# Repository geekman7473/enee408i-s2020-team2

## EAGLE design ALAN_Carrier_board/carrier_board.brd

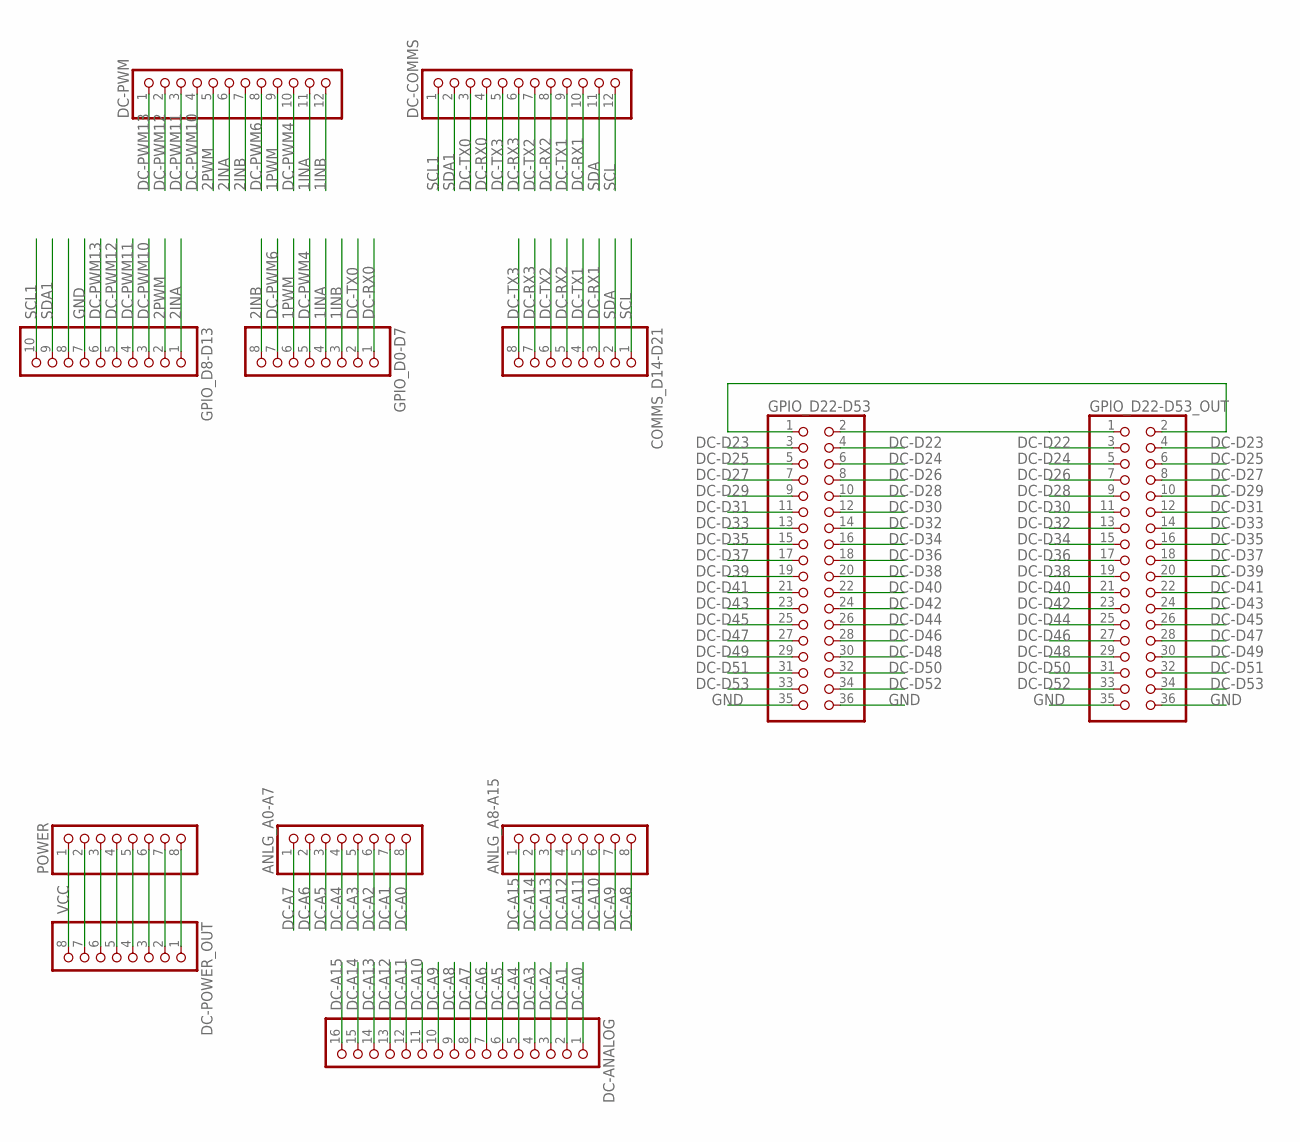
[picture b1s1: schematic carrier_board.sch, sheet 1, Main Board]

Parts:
ANLG_A0-A7, ANLG_A8-A15: PINHD-1X8; 1X08
COMMS_D14-D21: PINHD-1X8; 1X08
DC-ANALOG: PINHD-1X16; 1X16
DC-COMMS: PINHD-1X12; 1X12
DC-POWER_OUT: PINHD-1X8; 1X08
DC-PWM: PINHD-1X12; 1X12
GPIO_D0-D7: PINHD-1X8; 1X08
GPIO_D8-D13: PINHD-1X10; 1X10
GPIO_D22-D53, GPIO_D22-D53_OUT: PINHD-2X18; 2X18
POWER: PINHD-1X8; 1X08

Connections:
1INA: DC-PWM.11, GPIO_D0-D7.4; also elsewhere on the board
1INB: DC-PWM.12, GPIO_D0-D7.3; also elsewhere on the board
1PWM: DC-PWM.9, GPIO_D0-D7.6; also elsewhere on the board
2INA: DC-PWM.6, GPIO_D8-D13.1; also elsewhere on the board
2INB: DC-PWM.7, GPIO_D0-D7.8; also elsewhere on the board
2PWM: DC-PWM.5, GPIO_D8-D13.2; also elsewhere on the board
DC-A0: ANLG_A0-A7.8, DC-ANALOG.1
DC-A1: ANLG_A0-A7.7, DC-ANALOG.2
DC-A2: ANLG_A0-A7.6, DC-ANALOG.3
DC-A3: ANLG_A0-A7.5, DC-ANALOG.4
DC-A4: ANLG_A0-A7.4, DC-ANALOG.5
DC-A5: ANLG_A0-A7.3, DC-ANALOG.6
DC-A6: ANLG_A0-A7.2, DC-ANALOG.7
DC-A7: ANLG_A0-A7.1, DC-ANALOG.8
DC-A8: ANLG_A8-A15.8, DC-ANALOG.9
DC-A9: ANLG_A8-A15.7, DC-ANALOG.10
DC-A10: ANLG_A8-A15.6, DC-ANALOG.11
DC-A11: ANLG_A8-A15.5, DC-ANALOG.12
DC-A12: ANLG_A8-A15.4, DC-ANALOG.13
DC-A13: ANLG_A8-A15.3, DC-ANALOG.14
DC-A14: ANLG_A8-A15.2, DC-ANALOG.15
DC-A15: ANLG_A8-A15.1, DC-ANALOG.16
DC-D22: GPIO_D22-D53.4, GPIO_D22-D53_OUT.3
DC-D23: GPIO_D22-D53.3, GPIO_D22-D53_OUT.4
DC-D24: GPIO_D22-D53.6, GPIO_D22-D53_OUT.5
DC-D25: GPIO_D22-D53.5, GPIO_D22-D53_OUT.6
DC-D26: GPIO_D22-D53.8, GPIO_D22-D53_OUT.7
DC-D27: GPIO_D22-D53.7, GPIO_D22-D53_OUT.8
DC-D28: GPIO_D22-D53.10, GPIO_D22-D53_OUT.9
DC-D29: GPIO_D22-D53.9, GPIO_D22-D53_OUT.10
DC-D30: GPIO_D22-D53.12, GPIO_D22-D53_OUT.11
DC-D31: GPIO_D22-D53.11, GPIO_D22-D53_OUT.12
DC-D32: GPIO_D22-D53.14, GPIO_D22-D53_OUT.13
DC-D33: GPIO_D22-D53.13, GPIO_D22-D53_OUT.14
DC-D34: GPIO_D22-D53.16, GPIO_D22-D53_OUT.15
DC-D35: GPIO_D22-D53.15, GPIO_D22-D53_OUT.16
DC-D36: GPIO_D22-D53.18, GPIO_D22-D53_OUT.17
DC-D37: GPIO_D22-D53.17, GPIO_D22-D53_OUT.18
DC-D38: GPIO_D22-D53.20, GPIO_D22-D53_OUT.19
DC-D39: GPIO_D22-D53.19, GPIO_D22-D53_OUT.20
DC-D40: GPIO_D22-D53.22, GPIO_D22-D53_OUT.21
DC-D41: GPIO_D22-D53.21, GPIO_D22-D53_OUT.22
DC-D42: GPIO_D22-D53.24, GPIO_D22-D53_OUT.23
DC-D43: GPIO_D22-D53.23, GPIO_D22-D53_OUT.24
DC-D44: GPIO_D22-D53.26, GPIO_D22-D53_OUT.25
DC-D45: GPIO_D22-D53.25, GPIO_D22-D53_OUT.26
DC-D46: GPIO_D22-D53.28, GPIO_D22-D53_OUT.27
DC-D47: GPIO_D22-D53.27, GPIO_D22-D53_OUT.28
DC-D48: GPIO_D22-D53.30, GPIO_D22-D53_OUT.29
DC-D49: GPIO_D22-D53.29, GPIO_D22-D53_OUT.30
DC-D50: GPIO_D22-D53.32, GPIO_D22-D53_OUT.31
DC-D51: GPIO_D22-D53.31, GPIO_D22-D53_OUT.32
DC-D52: GPIO_D22-D53.34, GPIO_D22-D53_OUT.33
DC-D53: GPIO_D22-D53.33, GPIO_D22-D53_OUT.34
DC-PWM4: DC-PWM.10, GPIO_D0-D7.5
DC-PWM6: DC-PWM.8, GPIO_D0-D7.7
DC-PWM10: DC-PWM.4, GPIO_D8-D13.3
DC-PWM11: DC-PWM.3, GPIO_D8-D13.4
DC-PWM12: DC-PWM.2, GPIO_D8-D13.5
DC-PWM13: DC-PWM.1, GPIO_D8-D13.6
DC-RX0: DC-COMMS.4, GPIO_D0-D7.1
DC-RX1: COMMS_D14-D21.3, DC-COMMS.10
DC-RX2: COMMS_D14-D21.5, DC-COMMS.8
DC-RX3: COMMS_D14-D21.7, DC-COMMS.6
DC-TX0: DC-COMMS.3, GPIO_D0-D7.2
DC-TX1: COMMS_D14-D21.4, DC-COMMS.9
DC-TX2: COMMS_D14-D21.6, DC-COMMS.7
DC-TX3: COMMS_D14-D21.8, DC-COMMS.5
GND: GPIO_D8-D13.7, GPIO_D22-D53.35, GPIO_D22-D53.36, GPIO_D22-D53_OUT.35, GPIO_D22-D53_OUT.36; also elsewhere on the board
unnamed: GPIO_D22-D53.1, GPIO_D22-D53_OUT.2
unnamed: GPIO_D22-D53.2, GPIO_D22-D53_OUT.1
unnamed: DC-POWER_OUT.1, POWER.8
unnamed: DC-POWER_OUT.2, POWER.7
unnamed: DC-POWER_OUT.3, POWER.6
unnamed: DC-POWER_OUT.4, POWER.5
unnamed: DC-POWER_OUT.5, POWER.4
unnamed: DC-POWER_OUT.6, POWER.3
unnamed: DC-POWER_OUT.7, POWER.2
SCL: COMMS_D14-D21.1, DC-COMMS.12; also elsewhere on the board
SCL1: DC-COMMS.1, GPIO_D8-D13.10
SDA: COMMS_D14-D21.2, DC-COMMS.11; also elsewhere on the board
SDA1: DC-COMMS.2, GPIO_D8-D13.9
VCC: DC-POWER_OUT.8, POWER.1; also elsewhere on the board

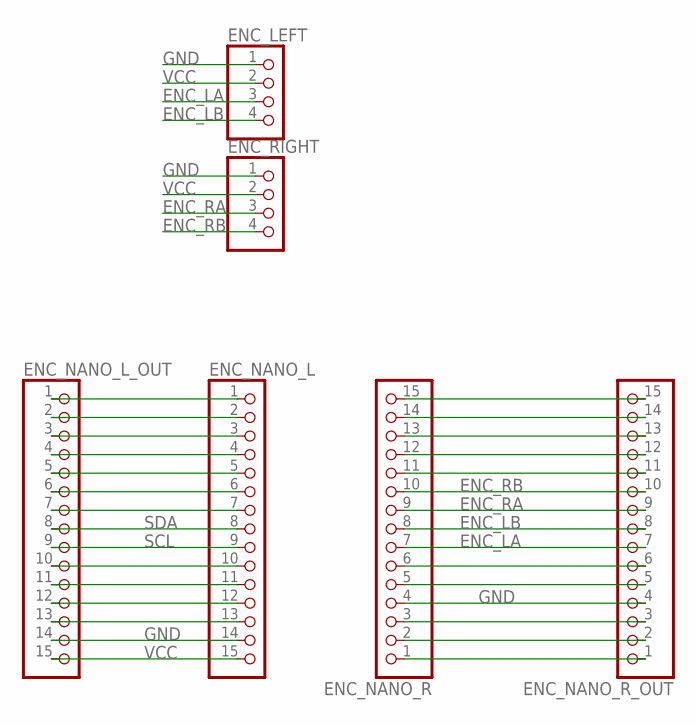
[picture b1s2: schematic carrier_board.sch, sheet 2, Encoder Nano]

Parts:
ENC_LEFT: PINHD-1X4/90; 1X04/90
ENC_NANO_L: PINHD-1X15; 1X15
ENC_NANO_L_OUT: PINHD-1X15; 1X15
ENC_NANO_R: PINHD-1X15; 1X15
ENC_NANO_R_OUT: PINHD-1X15; 1X15
ENC_RIGHT: PINHD-1X4/90; 1X04/90

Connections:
ENC_LA: ENC_LEFT.3, ENC_NANO_R.7, ENC_NANO_R_OUT.7
ENC_LB: ENC_LEFT.4, ENC_NANO_R.8, ENC_NANO_R_OUT.8
ENC_RA: ENC_NANO_R.9, ENC_NANO_R_OUT.9, ENC_RIGHT.3
ENC_RB: ENC_NANO_R.10, ENC_NANO_R_OUT.10, ENC_RIGHT.4
GND: ENC_LEFT.1, ENC_NANO_L.14, ENC_NANO_L_OUT.14, ENC_NANO_R.4, ENC_NANO_R_OUT.4, ENC_RIGHT.1; also elsewhere on the board
unnamed: ENC_NANO_L.13, ENC_NANO_L_OUT.13
unnamed: ENC_NANO_L.12, ENC_NANO_L_OUT.12
unnamed: ENC_NANO_L.11, ENC_NANO_L_OUT.11
unnamed: ENC_NANO_L.10, ENC_NANO_L_OUT.10
unnamed: ENC_NANO_L.7, ENC_NANO_L_OUT.7
unnamed: ENC_NANO_L.6, ENC_NANO_L_OUT.6
unnamed: ENC_NANO_L.5, ENC_NANO_L_OUT.5
unnamed: ENC_NANO_L.4, ENC_NANO_L_OUT.4
unnamed: ENC_NANO_L.3, ENC_NANO_L_OUT.3
unnamed: ENC_NANO_L.2, ENC_NANO_L_OUT.2
unnamed: ENC_NANO_L.1, ENC_NANO_L_OUT.1
unnamed: ENC_NANO_R.15, ENC_NANO_R_OUT.15
unnamed: ENC_NANO_R.14, ENC_NANO_R_OUT.14
unnamed: ENC_NANO_R.13, ENC_NANO_R_OUT.13
unnamed: ENC_NANO_R.12, ENC_NANO_R_OUT.12
unnamed: ENC_NANO_R.11, ENC_NANO_R_OUT.11
unnamed: ENC_NANO_R.6, ENC_NANO_R_OUT.6
unnamed: ENC_NANO_R.5, ENC_NANO_R_OUT.5
unnamed: ENC_NANO_R.3, ENC_NANO_R_OUT.3
unnamed: ENC_NANO_R.2, ENC_NANO_R_OUT.2
unnamed: ENC_NANO_R.1, ENC_NANO_R_OUT.1
SCL: ENC_NANO_L.9, ENC_NANO_L_OUT.9; also elsewhere on the board
SDA: ENC_NANO_L.8, ENC_NANO_L_OUT.8; also elsewhere on the board
VCC: ENC_LEFT.2, ENC_NANO_L.15, ENC_NANO_L_OUT.15, ENC_RIGHT.2; also elsewhere on the board

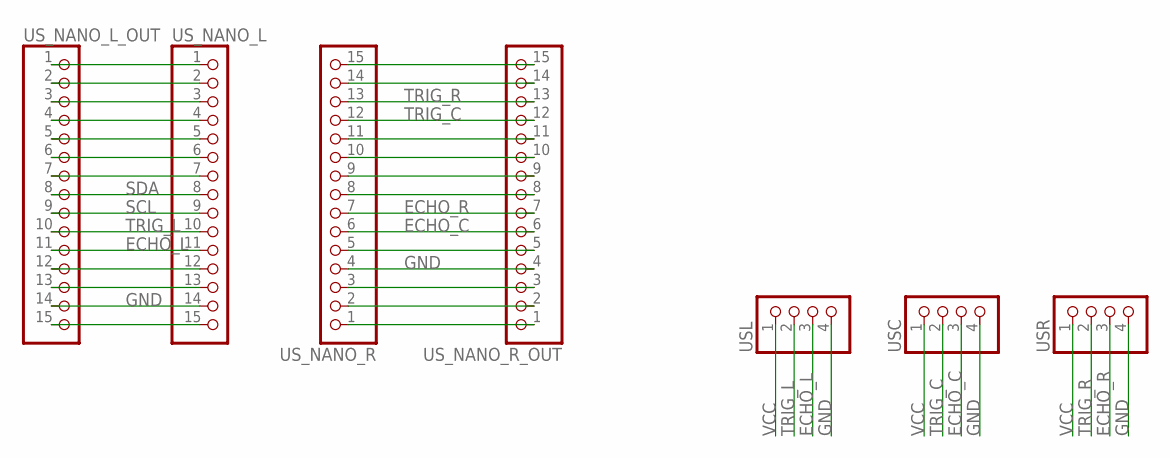
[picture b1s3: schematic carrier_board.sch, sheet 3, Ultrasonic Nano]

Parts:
USC: PINHD-1X4/90; 1X04/90
USL: PINHD-1X4/90; 1X04/90
USR: PINHD-1X4/90; 1X04/90
US_NANO_L: PINHD-1X15; 1X15
US_NANO_L_OUT: PINHD-1X15; 1X15
US_NANO_R: PINHD-1X15; 1X15
US_NANO_R_OUT: PINHD-1X15; 1X15

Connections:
ECHO_C: USC.3, US_NANO_R.6, US_NANO_R_OUT.6
ECHO_L: USL.3, US_NANO_L.11, US_NANO_L_OUT.11
ECHO_R: USR.3, US_NANO_R.7, US_NANO_R_OUT.7
GND: USC.4, USL.4, USR.4, US_NANO_L.14, US_NANO_L_OUT.14, US_NANO_R.4, US_NANO_R_OUT.4; also elsewhere on the board
unnamed: US_NANO_R.15, US_NANO_R_OUT.15
unnamed: US_NANO_R.14, US_NANO_R_OUT.14
unnamed: US_NANO_R.11, US_NANO_R_OUT.11
unnamed: US_NANO_R.10, US_NANO_R_OUT.10
unnamed: US_NANO_R.9, US_NANO_R_OUT.9
unnamed: US_NANO_R.8, US_NANO_R_OUT.8
unnamed: US_NANO_R.5, US_NANO_R_OUT.5
unnamed: US_NANO_R.3, US_NANO_R_OUT.3
unnamed: US_NANO_R.2, US_NANO_R_OUT.2
unnamed: US_NANO_R.1, US_NANO_R_OUT.1
unnamed: US_NANO_L.1, US_NANO_L_OUT.1
unnamed: US_NANO_L.2, US_NANO_L_OUT.2
unnamed: US_NANO_L.3, US_NANO_L_OUT.3
unnamed: US_NANO_L.4, US_NANO_L_OUT.4
unnamed: US_NANO_L.5, US_NANO_L_OUT.5
unnamed: US_NANO_L.6, US_NANO_L_OUT.6
unnamed: US_NANO_L.7, US_NANO_L_OUT.7
unnamed: US_NANO_L.12, US_NANO_L_OUT.12
unnamed: US_NANO_L.13, US_NANO_L_OUT.13
SCL: US_NANO_L.9, US_NANO_L_OUT.9; also elsewhere on the board
SDA: US_NANO_L.8, US_NANO_L_OUT.8; also elsewhere on the board
TRIG_C: USC.2, US_NANO_R.12, US_NANO_R_OUT.12
TRIG_L: USL.2, US_NANO_L.10, US_NANO_L_OUT.10
TRIG_R: USR.2, US_NANO_R.13, US_NANO_R_OUT.13
VCC: USC.1, USL.1, USR.1; also elsewhere on the board
VCC1: US_NANO_L.15, US_NANO_L_OUT.15

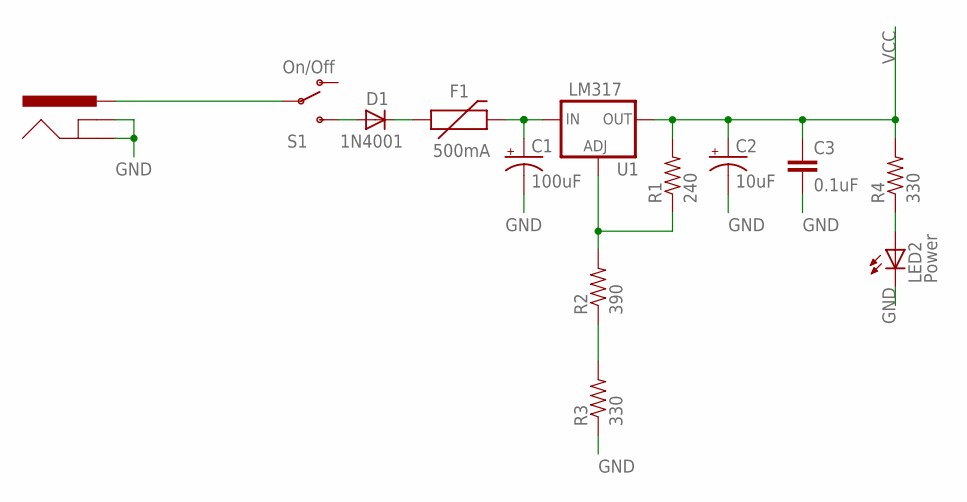
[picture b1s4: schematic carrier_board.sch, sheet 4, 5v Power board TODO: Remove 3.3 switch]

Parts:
C1: 100uF; CPOL-RADIAL-100UF-25V
C2: 10uF; CPOL-RADIAL-10UF-25V
C3: 0.1uF; CAP-PTH-SMALL2
D1: 1N4001; DIODE-0.4
F1: 500mA; PTC
J1: POWER_JACKPTH; POWER_JACK_PTH
LED2: Power; LED5MM
R1: 240; AXIAL-0.3
R2: 390; AXIAL-0.3
R3, R4: 330; AXIAL-0.3
S1: On/Off; SWITCH-SPST
U1: LM317; TO220-ADJ

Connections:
GND: C1.2 (-), C2.2 (-), C3.2, J1.GND, J1.GNDBREAK, LED2.K (C), R3.P$1 (1); also elsewhere on the board
unnamed: D1.C, F1.P$1 (1)
unnamed: D1.A, S1.3 (S)
unnamed: J1.PWR, S1.2
unnamed: R2.P$1 (1), R3.P$2 (2)
unnamed: R1.P$1 (1), R2.P$2 (2), U1.ADJ
unnamed: LED2.A, R4.P$1 (1)
RAW: C1.1 (+), F1.P$2 (2), U1.IN
VCC: C2.1 (+), C3.1, R1.P$2 (2), R4.P$2 (2), U1.OUT; also elsewhere on the board

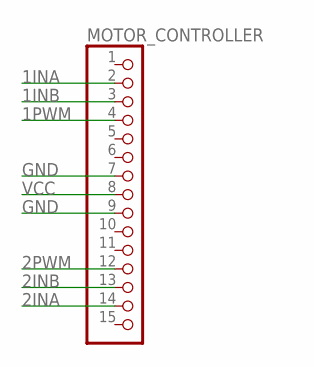
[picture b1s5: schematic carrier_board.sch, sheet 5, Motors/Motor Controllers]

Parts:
MOTOR_CONTROLLER: PINHD-1X15; 1X15

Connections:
1INA: MOTOR_CONTROLLER.2; also elsewhere on the board
1INB: MOTOR_CONTROLLER.3; also elsewhere on the board
1PWM: MOTOR_CONTROLLER.4; also elsewhere on the board
2INA: MOTOR_CONTROLLER.14; also elsewhere on the board
2INB: MOTOR_CONTROLLER.13; also elsewhere on the board
2PWM: MOTOR_CONTROLLER.12; also elsewhere on the board
GND: MOTOR_CONTROLLER.7, MOTOR_CONTROLLER.9; also elsewhere on the board
VCC: MOTOR_CONTROLLER.8; also elsewhere on the board

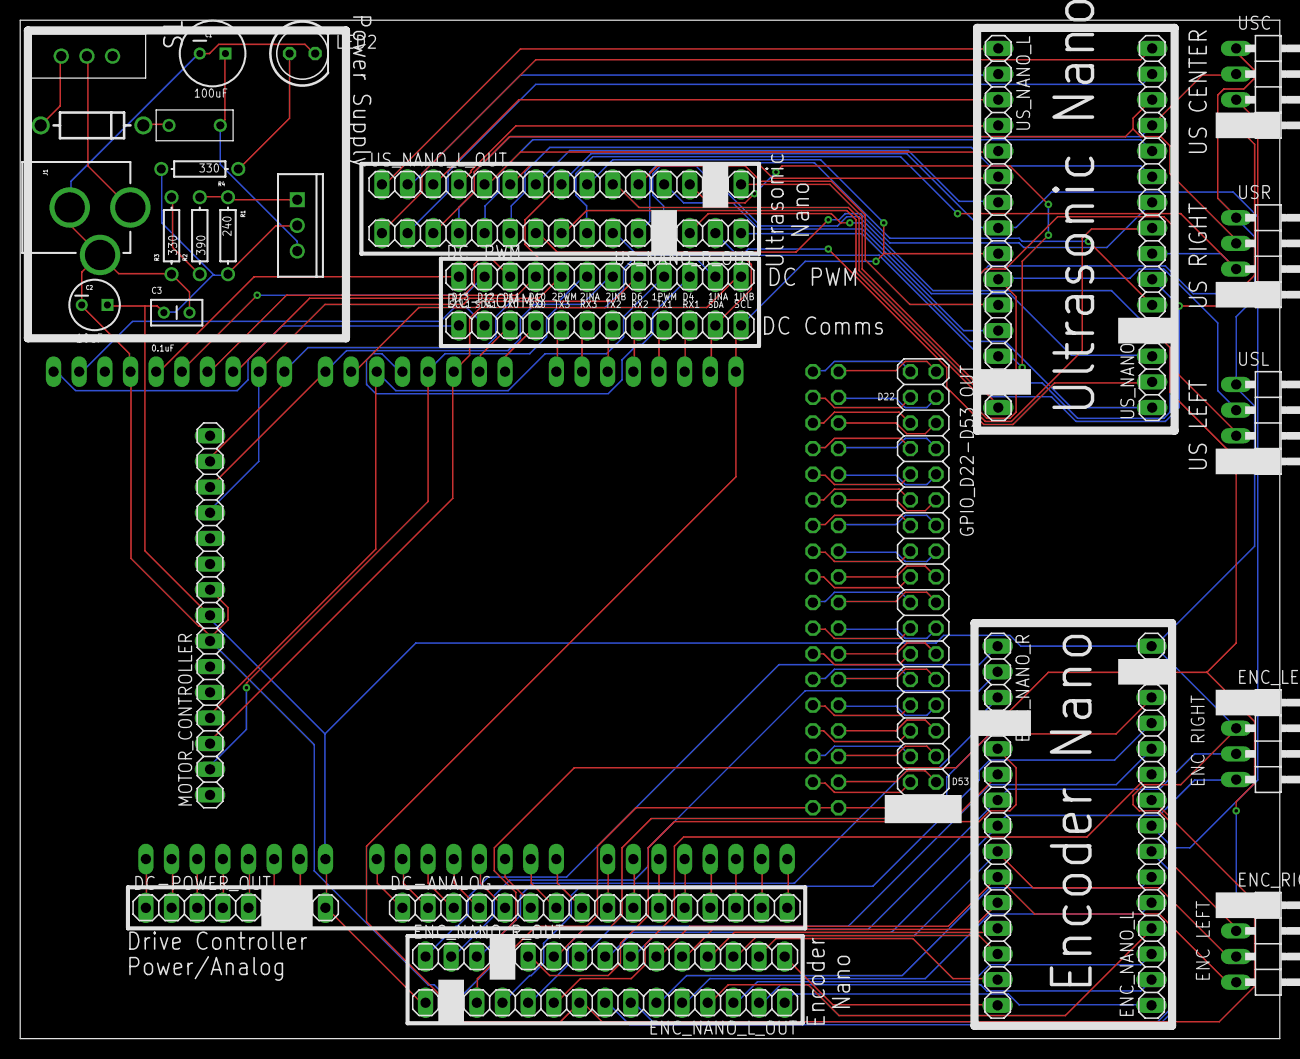
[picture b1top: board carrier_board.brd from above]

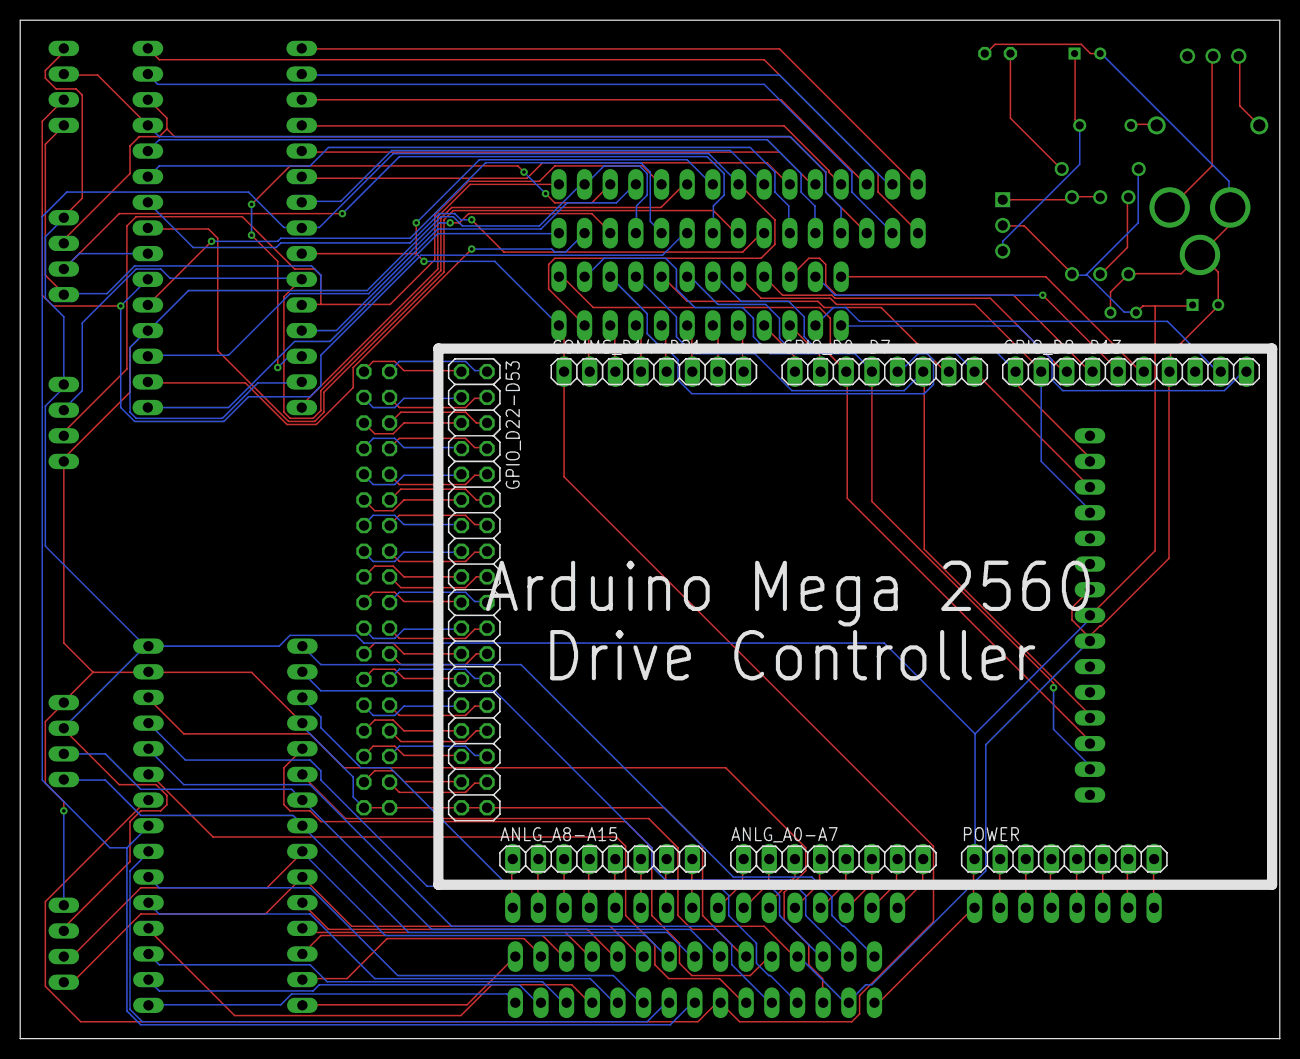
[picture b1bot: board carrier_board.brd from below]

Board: 2 copper layers, 124.7 x 100.8 mm, 39 parts (7 on the bottom side), 141 nets.

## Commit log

2020-01-29 Initial empty hpp files
2020-01-31 splitting arduino sketches
2020-02-02 Workingish print to serial
2020-02-02 Added encoder library
2020-02-02 Moved encoder library files
2020-02-02 working timer
2020-02-02 Semi-working
2020-02-02 Encoder now work
2020-02-02 Updated encoder processor to handle two encoders at once
2020-02-02 Added PID to drive_controller
2020-02-03 Working timer interrupt. TODO: calculate frequency and speed calculations
2020-02-04 Working i2c communication. Still missing speed calculations
2020-02-04 Driving forward
2020-02-04 fliped motors
2020-02-05 Commented out pinMode stuff
2020-02-13 Added serial control and PID in loop. TODO cleanup code quality
2020-02-17 Added ultrasonic code using interupts
2020-02-17 Library still broken. co-processor initial work
2020-02-18 Ultrasonic debugging
2020-02-19 Initial development, untested
2020-02-24 Finally got ultrasonics working
2020-02-25 Added I2C to ultrasonics
2020-02-25 Basic avoidance stuff
2020-02-25 Test TCB0
2020-02-26 Fixed pins
2020-02-28 Add unreviewed board
2020-02-28 Gitignore and latest files
2020-03-02 Decreased speed setting in basic avoidance
2020-03-03 Python code
2020-03-03 Changes to basic avoidance
2020-03-03 Fixed motor mismatch
2020-03-03 remove presets
2020-05-08 Alexa skill python code
    Read the instruction too
2020-05-08 Alexa skill python code
    The code has been commented for your convenience,
2020-05-09 pinout cleanup
2020-05-09 added pathplanning code
2020-05-10 cleanup of interop and improving planning tuning
2020-05-10 More code cleanup
2020-05-10 re-tuning PID and encoder params
2020-05-10 added yolo?
2020-05-10 moving code around
2020-05-11 naming and fixed relative imports
2020-05-11 Added straight line planning, driving at legos
